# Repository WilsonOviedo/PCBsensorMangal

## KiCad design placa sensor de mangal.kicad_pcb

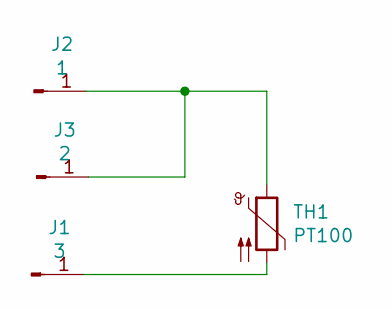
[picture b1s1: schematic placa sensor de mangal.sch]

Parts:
J1: 3; Pin_D1.4mm_L8.5mm_W2.8mm_FlatFork
J2: 1; Pin_D1.4mm_L8.5mm_W2.8mm_FlatFork
J3: 2; Pin_D1.4mm_L8.5mm_W2.8mm_FlatFork
TH1: PT100; R_Axial_DIN0204_L3.6mm_D1.6mm_P5.08mm_Horizontal

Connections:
unnamed: J1.1, TH1.2
unnamed: J2.1, J3.1, TH1.1

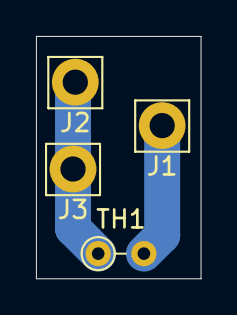
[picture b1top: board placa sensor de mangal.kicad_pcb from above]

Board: 2 copper layers, 9.1 x 13.5 mm, 4 parts (0 on the bottom side), 2 nets.

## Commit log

2021-05-01 Add archivos de placa
2021-05-01 version 1.0
2021-05-17 upgrade
2021-06-10 sin cambios
